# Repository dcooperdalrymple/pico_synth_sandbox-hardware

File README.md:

# pico_synth_sandbox-hardware
Raspberry Pi Pico digital synthesizer board with I2S or PWM audio, a PDM microphone, MIDI i/o, a capacitive keybed, 1602 display, a rotary encoder, and LiPo battery.

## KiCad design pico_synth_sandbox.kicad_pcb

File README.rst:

pico_synth_sandbox Hardware
===========================

.. image:: https://img.shields.io/badge/License-GPLv3-blue.svg
    :target: https://www.gnu.org/licenses/gpl-3.0
    :alt: GPL v3 License

Raspberry Pi Pico digital synthesizer board with stereo I2S audio (ADC & DAC), stereo omnidirectional MEMS microphones, MIDI i/o, a 16-key capacitive keybed, 1602 display, 2 rotary encoders, and LiPo battery charging and power distribution. Designed for use with CircuitPython and synthio.

.. list-table::

    * - .. image:: _static/front-side.jpg
            :alt: Front view of 3d rendered board
      - .. image:: _static/back-side.jpg
            :alt: Back view of 3d rendered board
      - .. image:: _static/bottom.jpg
            :alt: Bottom view of 3d rendered board

Features
--------

* PCM5102 I2S DAC with line output
* PCM1860 I2S ADC with line and microphone input
* PAM8019 amplifier with stereo class AB headphone and class D speaker output
* LiPo Battery usb charging and power supply controlled by 3v3_enable
* MIDI input and output via MIDI TRS-A 3.5mm jacks (compatible with most adapters)
* Input level potentiometer (line input only)
* Amplifier volume potentiometer (line output not included)
* 16 capacitive sense touch buttons powered by the TTP229-BSF
* 16x2 LCD character display
* 2 rotary encoders with push switches
* Micro SD card storage

Software
--------

CircuitPython Library
~~~~~~~~~~~~~~~~~~~~~

The pico_synth_sandbox is designed for use with CircuitPython and synthio. A specialized library with hardware abstraction and a multitude of additional features for embedded audio synthesis is available in the `pico_synth_sandbox <https://github.com/dcooperdalrymple/pico_synth_sandbox>`_ repository. Library documentation and other resources are available on `Read the Docs <https://pico-synth-sandbox.readthedocs.io/>`_.

CircuitPython Tests
~~~~~~~~~~~~~~~~~~~

A number of hardware tests are available within the ``./tests`` directory to validate the ``pico_synth_sandbox`` hardware using the REPL serial terminal.

RP2040 Pin Assignment
---------------------

Some pins require solder jumper configuration if you do not use the default pin assignment for MIDI & I2S.

.. list-table::
    :header-rows: 1

    * - Pin Reference
      - Assignment
      - Direction
      - Function

    * - GP0
      - SD Card RX
      - Input
      - SPI0
    * - GP1
      - SD Card CS
      - Output
      - SPI0
    * - GP2
      - SD Card SCK
      - Output
      - SPI0
    * - GP3
      - SD Card TX
      - Output
      - SPI0
    * - GP4
      - MIDITX
      - Output
      - UART1
    * - GP5
      - MIDIRX
      - Input
      - UART1
    * - GP6
      - 1602 Enable
      - Output
      - GPIO
    * - GP7
      - 1602 Reset
      - Output
      - GPIO
    * - GP8
      - ADC Serial Clock
      - Output
      - I2S
    * - GP9
      - ADC Word Select
      - Output
      - I2S
    * - GP10
      - ADC Serial Data
      - Input
      - I2S
    * - GP11
      - Encoder 1 A
      - Input
      - GPIO
    * - GP12
      - Encoder 1 B
      - Input
      - GPIO
    * - GP13
      - Encoder 1 Switch
      - Input
      - GPIO
    * - GP14
      - TTP229 Serial Data
      - Input
      - GPIO
    * - GP15
      - TTP229 Serial Clock
      - Output
      - GPIO
    * - GP16
      - Encoder 2 A
      - Input
      - GPIO
    * - GP17
      - Encoder 2 B
      - Input
      - GPIO
    * - GP18
      - Encoder 2 Switch
      - Input
      - GPIO
    * - GP19
      - DAC Serial Clock
      - Output
      - I2S
    * - GP20
      - DAC Word Select
      - Output
      - I2S
    * - GP21
      - DAC Serial Data
      - Output
      - I2S
    * - GP22
      - 1602 D4
      - Output
      - GPIO
    * - GP26
      - 1602 D5
      - Output
      - GPIO
    * - GP27
      - 1602 D6
      - Output
      - GPIO
    * - GP28
      - 1602 D7
      - Output
      - GPIO

Schematic
---------

.. image:: _static/schematic.jpg
   :alt: Hardware schematic of pico_synth_sandbox device
   :target: _static/schematic.pdf

Attribution
-----------

* Project inspired by `todbot/pico_test_synth <https://github.com/todbot/pico_test_synth>`_

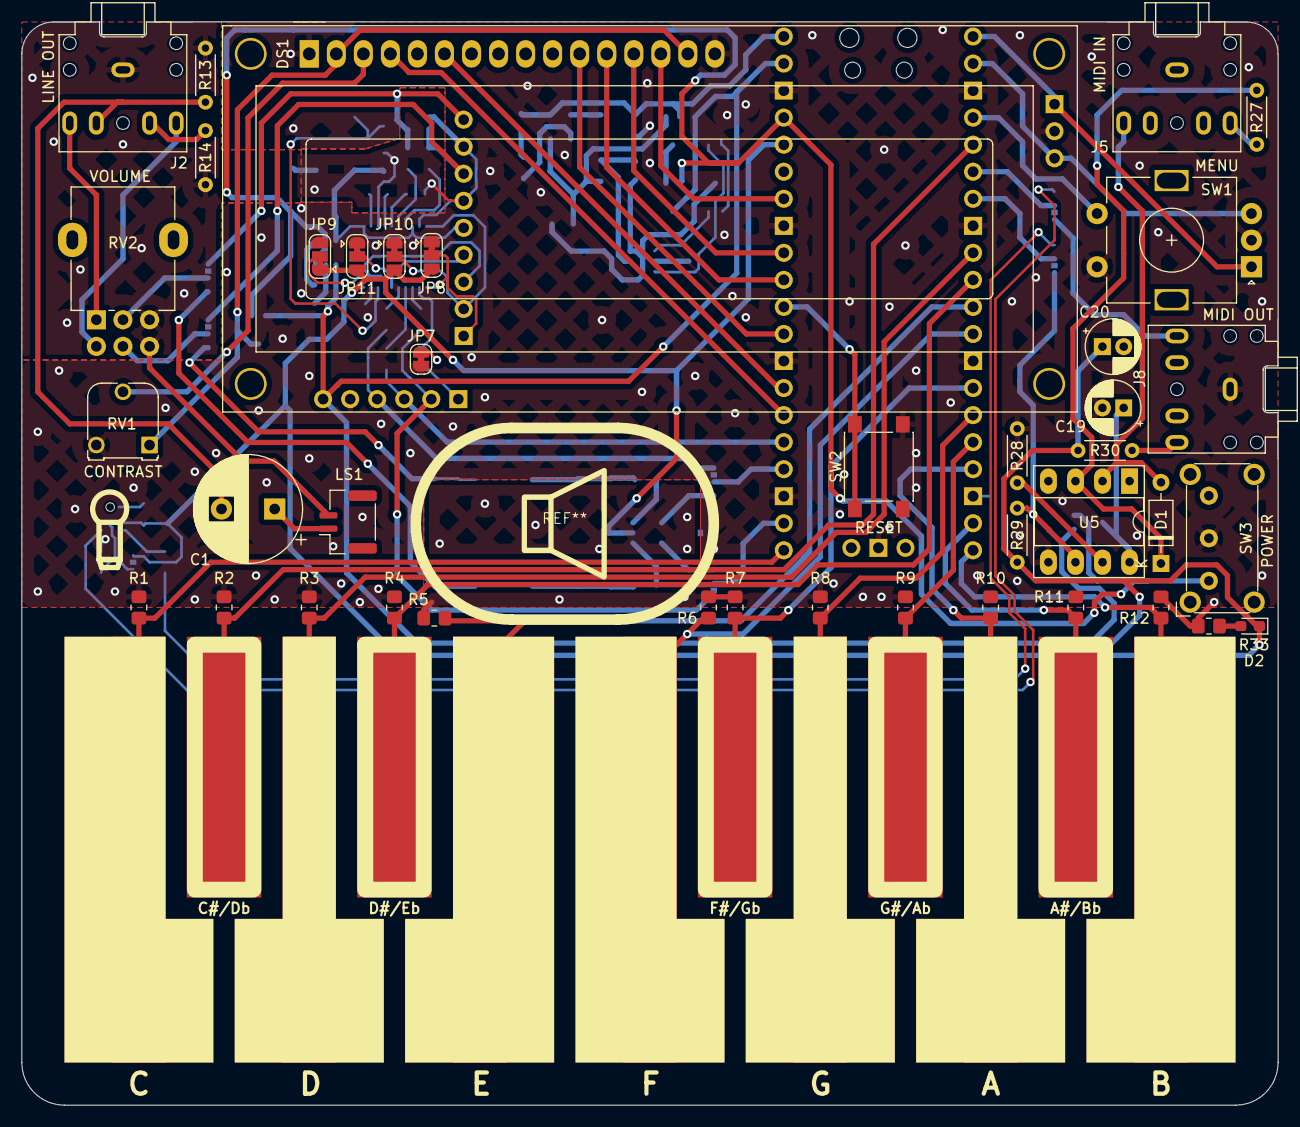
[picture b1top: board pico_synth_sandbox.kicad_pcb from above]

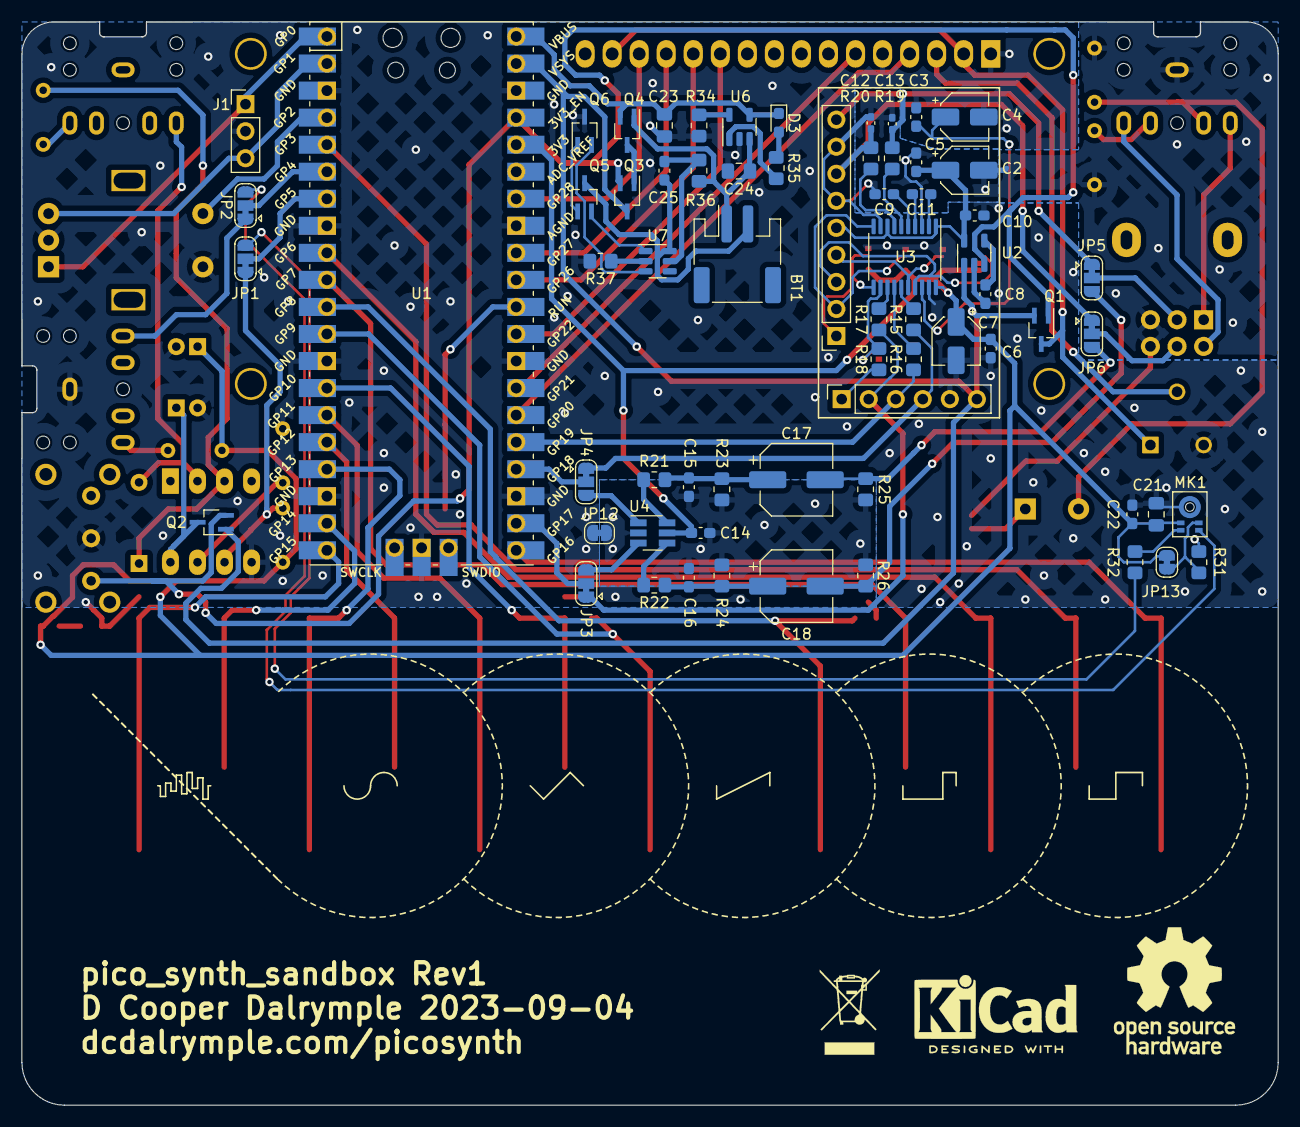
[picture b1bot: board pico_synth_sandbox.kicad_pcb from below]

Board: 2 copper layers, 118.0 x 101.7 mm, 118 parts (66 on the bottom side), 96 nets.

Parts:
BT1: LiPo Battery; JST_PH_S2B-PH-SM4-TB_1x02-1MP_P2.00mm_Horizontal
C1: 220uF; CP_Radial_D10.0mm_P5.00mm
C2, C4, C7: 10uF; CP_Elec_4x5.4
C3, C5, C6, C14, C15, C16, C22, C25: 0.1uF; C_0603_1608Metric_Pad1.08x0.95mm_HandSolder
C8: 470pF; C_0603_1608Metric_Pad1.08x0.95mm_HandSolder
C9, C10, C11: 2.2uF; C_0603_1608Metric_Pad1.08x0.95mm_HandSolder
C12, C13: 2.2nF; C_0402_1005Metric_Pad0.74x0.62mm_HandSolder
C17, C18: 47uF; CP_Elec_6.3x5.7
C19, C20: 1uF; CP_Radial_D5.0mm_P2.00mm
C21, C23, C24: 10uF; C_0805_2012Metric_Pad1.18x1.45mm_HandSolder
D1: 1N914; D_DO-35_SOD27_P7.62mm_Horizontal
D2: PWR; LED_0603_1608Metric_Pad1.05x0.95mm_HandSolder
D3: CHRG; LED_0603_1608Metric_Pad1.05x0.95mm_HandSolder
DS1: WC1602A
J1: UART0; PinHeader_1x03_P2.54mm_Vertical
J2: LINEOUT; Jack_3.5mm_CUI_SJ1-3525N_Horizontal
J3: M-BUS; PinSocket_1x06_P2.54mm_Vertical
J4: A-BUS; PinSocket_1x09_P2.54mm_Vertical
J5: MIDIIN; Jack_3.5mm_CUI_SJ1-3525N_Horizontal
J8: MIDIOUT; Jack_3.5mm_CUI_SJ1-3525N_Horizontal
JP1: PDMDAT; SolderJumper-3_P1.3mm_Bridged12_RoundedPad1.0x1.5mm
JP2: PDMCLK; SolderJumper-3_P1.3mm_Bridged12_RoundedPad1.0x1.5mm
JP3: I2SPWML; SolderJumper-3_P1.3mm_Bridged12_RoundedPad1.0x1.5mm
JP4: I2SPWMR; SolderJumper-3_P1.3mm_Bridged12_RoundedPad1.0x1.5mm
JP5: ALJP; SolderJumper-3_P1.3mm_Bridged12_RoundedPad1.0x1.5mm
JP6: ARJP; SolderJumper-3_P1.3mm_Bridged12_RoundedPad1.0x1.5mm
JP7: SCK; SolderJumper-2_P1.3mm_Bridged_RoundedPad1.0x1.5mm
JP8: H1L; SolderJumper-3_P1.3mm_Bridged12_RoundedPad1.0x1.5mm
JP9: H3L; SolderJumper-3_P1.3mm_Bridged12_RoundedPad1.0x1.5mm
JP10: H2L; SolderJumper-3_P1.3mm_Bridged12_RoundedPad1.0x1.5mm
JP11: H4L; SolderJumper-3_P1.3mm_Bridged12_RoundedPad1.0x1.5mm
JP12: SolderJumper_2_Bridged; SolderJumper-2_P1.3mm_Bridged_RoundedPad1.0x1.5mm
JP13: PDMSEL; SolderJumper-2_P1.3mm_Bridged_RoundedPad1.0x1.5mm
LS1: Speaker; JST_GH_SM02B-GHS-TB_1x02-1MP_P1.25mm_Horizontal
MK1: IM69D130; Infineon_PG-LLGA-5-1
Q1, Q2, Q3, Q5, Q6: NMOS; SOT-323_SC-70_Handsoldering
Q4: PMOS; SOT-323_SC-70_Handsoldering
R1, R2, R3, R4, R5, R6, R7, R8, R9, R10, R11, R12: 1M; R_0805_2012Metric_Pad1.20x1.40mm_HandSolder
R13, R14: 10k; R_Axial_DIN0204_L3.6mm_D1.6mm_P5.08mm_Horizontal
R15, R16, R17, R18: 22; R_0805_2012Metric_Pad1.20x1.40mm_HandSolder
R19, R20: 470; R_0805_2012Metric_Pad1.20x1.40mm_HandSolder
R21, R22: 220; R_0805_2012Metric_Pad1.20x1.40mm_HandSolder
R23, R24, R32: 100; R_0805_2012Metric_Pad1.20x1.40mm_HandSolder
R25, R26: 1.8k; R_0805_2012Metric_Pad1.20x1.40mm_HandSolder
R27, R30: 220; R_Axial_DIN0204_L3.6mm_D1.6mm_P5.08mm_Horizontal
R28: 4.7k; R_Axial_DIN0204_L3.6mm_D1.6mm_P5.08mm_Horizontal
R29: 470; R_Axial_DIN0204_L3.6mm_D1.6mm_P5.08mm_Horizontal
R31: 10k; R_0805_2012Metric_Pad1.20x1.40mm_HandSolder
R33, R35: 1k; R_0805_2012Metric_Pad1.20x1.40mm_HandSolder
R34: 4.7k; R_0805_2012Metric_Pad1.20x1.40mm_HandSolder
R36: 330; R_0805_2012Metric_Pad1.20x1.40mm_HandSolder
R37: 2.7k; R_0805_2012Metric_Pad1.20x1.40mm_HandSolder
RV1: 10k; Potentiometer_Runtron_RM-065_Vertical
RV2: 100k; Potentiometer_Alpha_RD902F-40-00D_Dual_Vertical
SW1: RotaryEncoder_Switch; RotaryEncoder_Alps_EC11E-Switch_Vertical_H20mm
SW2: RESET; SW_Push_1P1T_NO_6x6mm_H9.5mm
SW3: PWR_EN; SW_E-Switch_EG1224_SPDT_Angled
TP1: C; CapKeysWhiteLeft
TP2: C#/Db; CapKeysBlack
TP3: D; CapKeysWhiteMiddle
TP4: D#/Eb; CapKeysBlack
TP5: E; CapKeysWhiteRight
TP6: F; CapKeysWhiteLeft
TP7: F#/Gb; CapKeysBlack
TP8: G; CapKeysWhiteMiddle
TP9: G#/Ab; CapKeysBlack
TP10: A; CapKeysWhiteMiddle
TP11: A#/Bb; CapKeysBlack
TP12: B; CapKeysWhiteRight
U1: Pico; RPi_Pico_SMD_TH
U2: MIC5219-3.3YM5; SOT-23-5
U3: PCM5102A; TSSOP-20_4.4x6.5mm_P0.65mm
U4: 74AUC2G34; SOT-23-6_Handsoldering
U5: 6N138; DIP-8_W7.62mm_Socket_LongPads
U6: MCP73831-5-OT; SOT-23-5
U7: AP9101CK6; SOT-23-6

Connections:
+3.3V: C6.1, C7.1, C14.1, C20.1, C21.1, C22.1, D2.1 (K), JP8.3 (B), JP9.1 (A), JP10.3 (B), JP11.3 (B), JP13.2 (B), MK1.2 (VDD), R29.1, R30.1, U1.36 (3V3), U3.20 (DVDD), U4.5 (VCC)
+3.3VA: C2.1, C5.1, C10.1, J4.5, U2.5 (OUT), U3.1 (CPVDD), U3.8 (AVDD)
+BATT: BT1.1 (+), C24.1, Q4.1 (D), R36.1, U6.3 (V_{BAT})
-BATT: BT1.2 (-), C25.2, Q5.3 (S), U7.6 (VSS)
/1602D4: DS1.14 (D7), U1.34 (GPIO28_ADC2)
/1602D5: DS1.13 (D6), U1.32 (GPIO27_ADC1)
/1602D6: DS1.12 (D5), U1.31 (GPIO26_ADC0)
/1602D7: DS1.11 (D4), U1.29 (GPIO22)
/1602EN: DS1.6 (E), U1.27 (GPIO21)
/1602RS: DS1.4 (RS), U1.26 (GPIO20)
/ENCA: J1.1, SW1.A, U1.1 (GPIO0)
/ENCB: J1.3, SW1.B, U1.2 (GPIO1)
/I2S Audio/DEMP: J4.2, JP10.2 (C), U3.10 (DEMP)
/I2S Audio/FLT: J4.1, JP8.2 (C), U3.11 (FLT)
/I2S Audio/FMT: J4.4, JP11.2 (C), U3.16 (FMT)
/I2S Audio/LDOO: C3.1, C4.1, U3.18 (LDOO)
/I2S Audio/SCK: J3.1, R18.1
/I2S Audio/XSMT: J4.3, JP9.2 (C), U3.17 (XSMT)
/SWA: SW1.S1, U1.4 (GPIO2)
/TPAD1: R1.1, TP1.1, U1.21 (GPIO16)
/TPAD2: R2.1, TP2.1, U1.5 (GPIO3)
/TPAD3: R3.1, TP3.1, U1.9 (GPIO6)
/TPAD4: R4.1, TP4.1, U1.10 (GPIO7)
/TPAD5: R5.1, TP5.1, U1.11 (GPIO8)
/TPAD6: R6.1, TP6.1, U1.12 (GPIO9)
/TPAD7: R7.1, TP7.1, U1.14 (GPIO10)
/TPAD8: R8.1, TP8.1, U1.15 (GPIO11)
/TPAD9: R9.1, TP9.1, U1.16 (GPIO12)
/TPAD10: R10.1, TP10.1, U1.17 (GPIO13)
/TPAD11: R11.1, TP11.1, U1.19 (GPIO14)
/TPAD12: R12.1, TP12.1, U1.20 (GPIO15)
GND: C3.2, C4.2, C6.2, C7.2, C8.2, C10.2, C19.2, C20.2, C21.2, C22.2, C23.2, C24.2, DS1.1 (VSS), DS1.5 (R/W), DS1.16 (LED(-)), J1.2, J3.5, J8.S, JP7.1 (A), JP8.1 (A), JP9.3 (B), JP10.1 (A), JP11.1 (A), JP12.1 (A), MK1.5 (GND), Q6.3 (S), R1.2, R2.2, R3.2, R4.2, R5.2, R6.2, R7.2, R8.2, R9.2, R10.2, R11.2, R12.2, R28.2, R31.2, R33.2, R34.2, R37.2, RV1.3, SW1.C, SW1.S2, SW2.2, SW3.2 (B), U1.3 (GND), U1.8 (GND), U1.13 (GND), U1.18 (GND), U1.23 (GND), U1.28 (GND), U1.33 (AGND), U1.38 (GND), U1.42 (GND), U2.2 (GND), U3.19 (DGND), U5.5 (GND), U6.2 (V_{SS})
GNDA: C2.2, C5.2, C9.2, C12.2, C13.2, J2.S, J4.6, J4.8, LS1.2, R13.2, R14.2, RV2.3, RV2.6, U3.3 (CPGND), U3.9 (AGND)
GNDD: C14.2, C15.1, C16.1, JP12.2 (B), R23.1, R24.1, R25.1, R26.1, U4.2 (GND)
I2SAL: C13.1, J4.9, JP5.1 (A), R19.1
I2SAR: C12.1, J4.7, JP6.1 (A), R20.1
I2SCLK: J3.2, JP3.1 (A), R17.1
I2SDAT: J3.3, R16.1, U1.25 (GPIO19)
I2SWS: J3.4, JP4.1 (A), R15.1
MICCLK: JP2.3 (B), MK1.3 (CLOCK)
MICDAT: JP1.3 (B), R32.2
MIDIRX: JP1.1 (A), R29.2, U5.6 (VO2)
MIDITX: J8.T, JP2.1 (A)
unnamed: C1.1, LS1.1
unnamed: C1.2, J2.TN, R13.1
unnamed: C15.2, C17.1, R21.1, R23.2
unnamed: C16.2, C18.1, R22.1, R24.2
unnamed: D1.2 (A), J5.T, U5.2 (C1)
unnamed: D1.1 (K), R27.2, U5.3 (C2)
unnamed: D2.2 (A), R33.1
unnamed: D3.2 (A), R35.1
unnamed: DS1.2 (VDD), DS1.15 (LED(+)), Q1.3 (S), RV1.1
unnamed: DS1.3 (VO), RV1.2
unnamed: J2.R, RV2.4
unnamed: J2.RN, R14.1
unnamed: J2.T, RV2.1
unnamed: J5.R, R27.1
unnamed: J8.R, R30.2
unnamed: JP1.2 (C), U1.7 (GPIO5)
unnamed: JP2.2 (C), U1.6 (GPIO4)
unnamed: JP3.2 (C), U1.22 (GPIO17)
unnamed: JP4.2 (C), U1.24 (GPIO18)
unnamed: JP5.2 (C), RV2.2
unnamed: JP6.2 (C), RV2.5
unnamed: JP7.2 (B), R18.2, U3.12 (SCK)
unnamed: JP13.1 (A), MK1.4 (SELECT), R31.1
unnamed: MK1.1 (DATA), R32.1
unnamed: C19.1, Q2.3 (S), U5.8 (VCC)
unnamed: Q5.1 (D), Q6.1 (D)
unnamed: Q5.2 (G), U7.1 (DO)
unnamed: Q6.2 (G), U7.3 (CO)
unnamed: R21.2, U4.6
unnamed: R22.2, U4.4
unnamed: C8.1, U2.4 (BP)
unnamed: R17.2, U3.13 (BCK)
unnamed: C11.2, U3.4 (CAPM)
unnamed: C11.1, U3.2 (CAPP)
unnamed: R16.2, U3.14 (DIN)
unnamed: R15.2, U3.15 (LRCK)
unnamed: R19.2, U3.6 (OUTL)
unnamed: R20.2, U3.7 (OUTR)
unnamed: C9.1, U3.5 (VNEG)
unnamed: R28.1, U5.7 (VO1)
unnamed: R34.1, U6.5 (PROG)
unnamed: R35.2, U6.1 (STAT)
unnamed: C25.1, R36.2, U7.5 (VDD)
unnamed: R37.1, U7.2 (VM)
PWMAL: C18.2, JP5.3 (B), R26.2
PWMAR: C17.2, JP6.3 (B), R25.2
PWMDL: JP3.3 (B), U4.3
PWMDR: JP4.3 (B), U4.1
PWR_EN: Q1.1 (D), Q2.2 (G), Q3.2 (G), SW3.1 (A), U1.37 (3V3_EN), U2.3 (EN)
RUN: SW2.1, U1.30 (RUN)
VBUS: C23.1, D3.1 (K), Q4.2 (G), U1.40 (VBUS), U6.4 (V_{DD})
VSYS: J3.6, Q1.2 (G), Q2.1 (D), Q3.3 (S), U1.39 (VSYS), U2.1 (IN)
VSYS&VBAT: Q3.1 (D), Q4.3 (S)

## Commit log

2023-11-14 Migrated from `pico_synth_sandbox` repository.
2023-11-14 Converted markdown to restructuredtext.
2023-11-14 Fixed formatting issues in readme.
2023-11-15 Added CircuitPython test for TonTouch TTP229 IC.
2023-12-13 Added notice to README about upcoming hardware revision.
2024-01-01 Revision 2 of schematic and pcb.
2024-01-02 Added additional 3d models to pcb.
2024-01-02 Rev2 renders and schematic.
2024-01-02 Rev1 3d printed case.
2024-01-02 Updated README for revision 2.
2024-01-02 Fixed I2S global label direction in schematic.
2024-01-03 Removed FreeCAD backups.
2024-01-10 Improved capacitor spacing around battery connector.
2024-01-10 Battery orientation indicators added to silkscreen.
2024-01-16 Fixed character lcd data pin references.
2024-01-16 Updated rotary encoder test for Rev2.
2024-01-17 Simple stencil jig (rev2)
2024-01-17 Removed unnecessary tests and updated pin assignments.
2024-01-17 Various minor schematic updates.
2024-01-17 SD card storage test.
2024-01-30 Micropython tests to assess i2s audio input and output.
2024-01-30 Updated pin allocations for more CircuitPython tests.
2024-02-06 3D printed case design for Rev2.
2024-02-21 Minor update to ADC connection.
2024-09-08 Updated to KiCad 8.0 and fixed TTP229 3.3v net.
2024-09-08 Updated to Kicad v8.0.
2024-09-08 Fixed error with TTP229BSF power input.
2024-09-08 Removed temporary projects.
